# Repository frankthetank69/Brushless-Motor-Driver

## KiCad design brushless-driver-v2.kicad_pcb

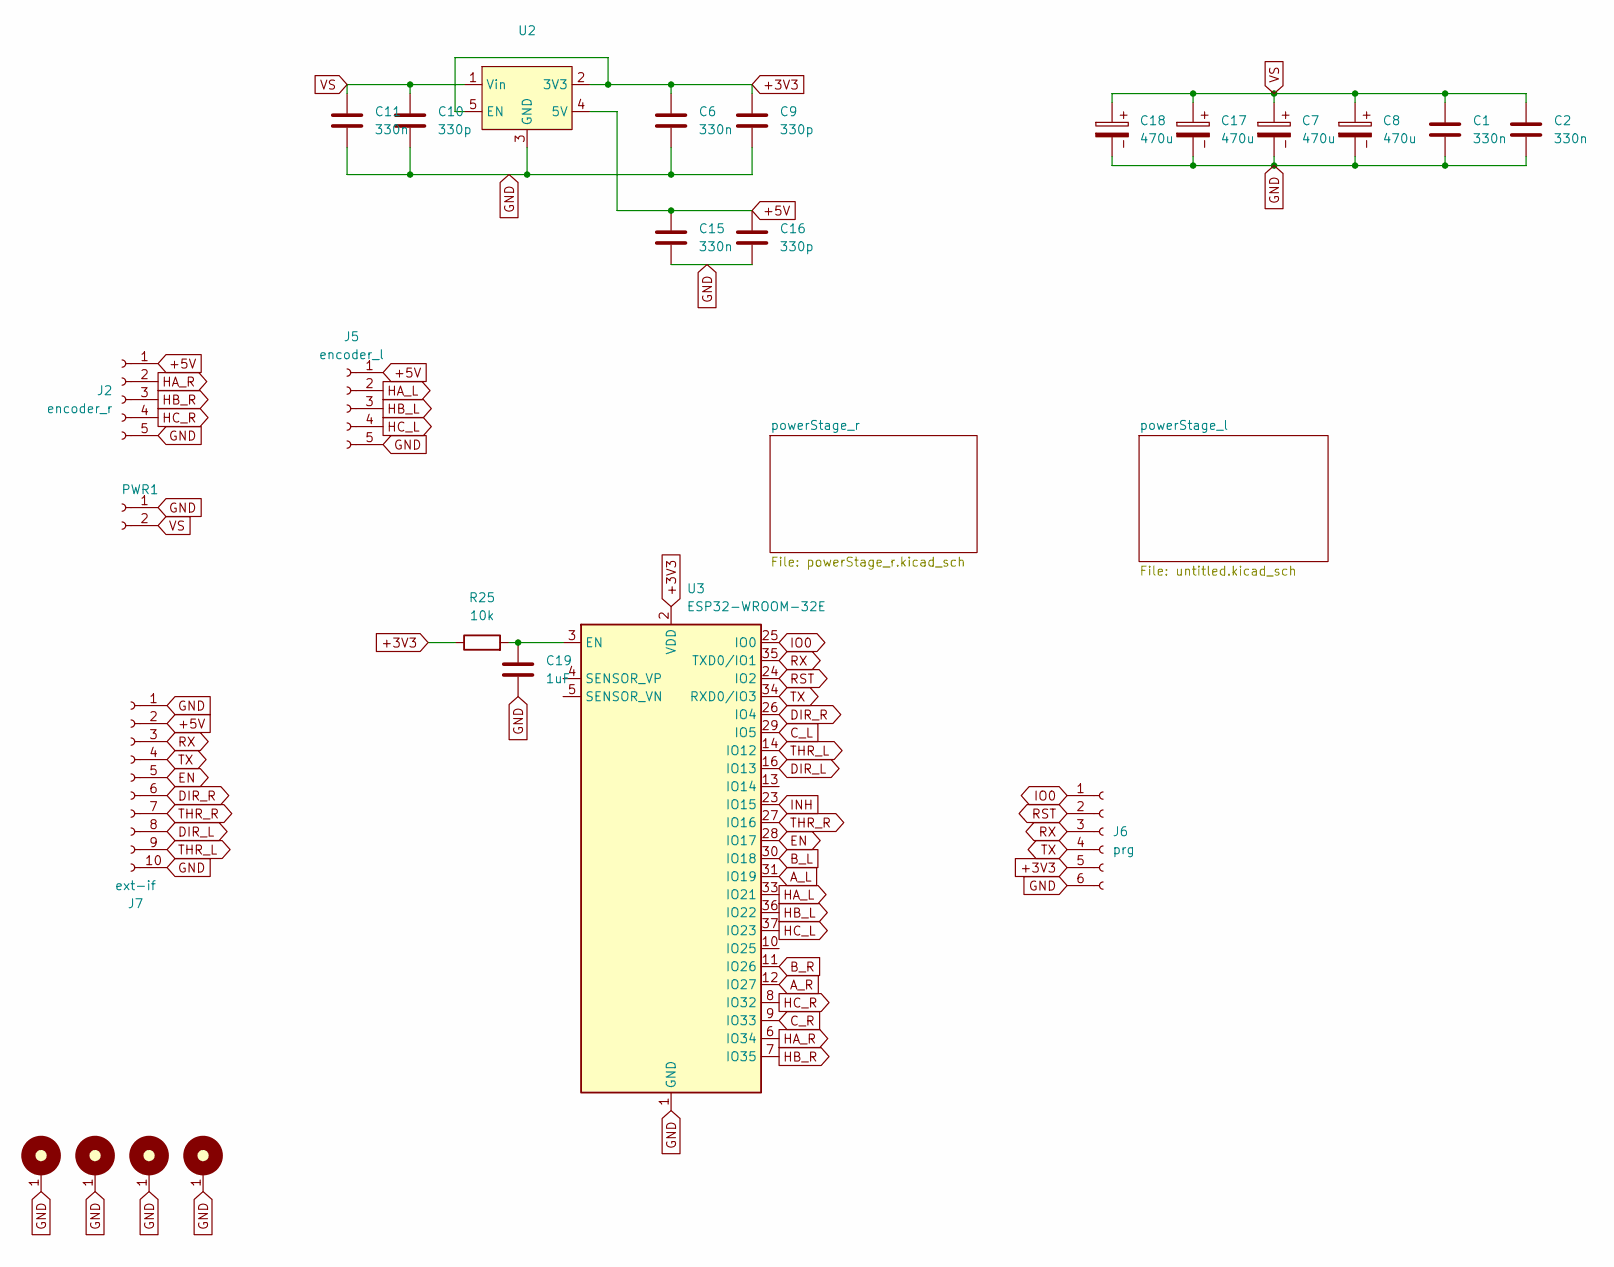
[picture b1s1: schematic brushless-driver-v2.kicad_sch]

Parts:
C1, C2, C6, C11, C15: 330n; C_0805_2012Metric_Pad1.18x1.45mm_HandSolder
C7, C8, C17, C18: 470u; CP_Radial_D10.0mm_P5.00mm
C9, C10, C16: 330p; C_0805_2012Metric_Pad1.18x1.45mm_HandSolder
C19: 1uF; C_0805_2012Metric_Pad1.18x1.45mm_HandSolder
H1, H2, H3, H4: MountingHole_M3_3.2mm_Pad; MountingHole_3.5mm_Pad_Via
J2: encoder_r; JST_PH_S5B-PH-K_1x05_P2.00mm_Horizontal
J5: encoder_l; JST_PH_S5B-PH-K_1x05_P2.00mm_Horizontal
J6: prg; Wannenstecker_6pin
J7: ext-if; Wannenstecker_10pin
PWR1: Conn_01x02_Socket; TerminalBlock_MaiXu_MX126-5.0-02P_1x02_P5.00mm
R25: 10k; R_0805_2012Metric_Pad1.20x1.40mm_HandSolder
U2: TO-252-5-11
U3: ESP32-WROOM-32E; ESP32-WROOM-32D

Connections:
+3V3: C6.1, C9.1, J6.5, R25.1, U2.2 (3V3), U2.5 (EN), U3.2 (VDD); also elsewhere on the board
+5V: C15.1, C16.1, J2.1, J5.1, J7.2, U2.4 (5V)
DIR_L: J7.8, U3.16 (IO13); also elsewhere on the board
DIR_R: J7.6, U3.26 (IO4); also elsewhere on the board
EN: J7.5, U3.28 (IO17); also elsewhere on the board
GND: C1.2, C2.2, C6.2, C7.2, C8.2, C9.2, C10.2, C11.2, C15.2, C16.2, C17.2, C18.2, C19.2, H1.1, H2.1, H3.1, H4.1, J2.5, J5.5, J6.6, J7.1, J7.10, PWR1.1, U2.3 (GND), U3.1 (GND), U3.15 (GND), U3.38 (GND), U3.39 (GND); also elsewhere on the board
HA_L: J5.2, U3.33 (IO21); also elsewhere on the board
HA_R: J2.2, U3.6 (IO34); also elsewhere on the board
HB_L: J5.3, U3.36 (IO22); also elsewhere on the board
HB_R: J2.3, U3.7 (IO35); also elsewhere on the board
HC_L: J5.4, U3.37 (IO23); also elsewhere on the board
HC_R: J2.4, U3.8 (IO32); also elsewhere on the board
IO0: J6.1, U3.25 (IO0); also elsewhere on the board
unnamed 50: C19.1, R25.2, U3.3 (EN); also elsewhere on the board
RST: J6.2, U3.24 (IO2); also elsewhere on the board
RX: J6.3, J7.3, U3.35 (TXD0/IO1); also elsewhere on the board
THR_L: J7.9, U3.14 (IO12); also elsewhere on the board
THR_R: J7.7, U3.27 (IO16); also elsewhere on the board
TX: J6.4, J7.4, U3.34 (RXD0/IO3); also elsewhere on the board
VS: C1.1, C2.1, C7.1, C8.1, C10.1, C11.1, C17.1, C18.1, PWR1.2, U2.1 (Vin); also elsewhere on the board

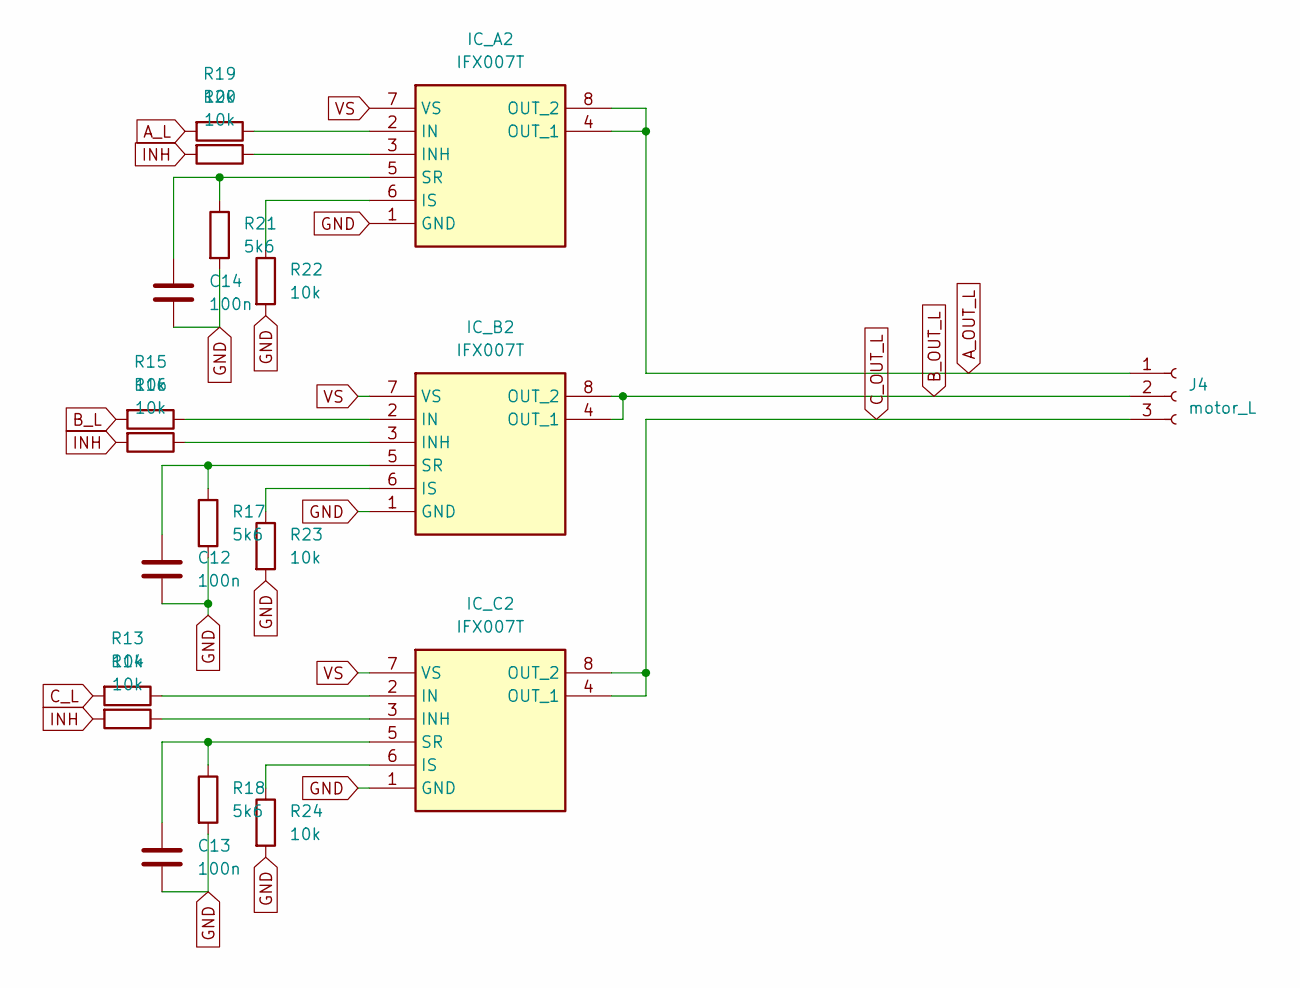
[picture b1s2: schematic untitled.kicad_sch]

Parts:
C12, C13, C14: 100n; C_0805_2012Metric_Pad1.18x1.45mm_HandSolder
IC_A2: IFX007T; TO-263-7_TabPin4; Manufacturer_Part_Number IFX007TAUMA1; Mouser Part Number 726-IFX007TAUMA1
IC_B2: IFX007T; TO-263-7_TabPin4; Manufacturer_Part_Number IFX007TAUMA1; Mouser Part Number 726-IFX007TAUMA1
IC_C2: IFX007T; TO-263-7_TabPin4; Manufacturer_Part_Number IFX007TAUMA1; Mouser Part Number 726-IFX007TAUMA1
J4: motor_L; TerminalBlock_MaiXu_MX126-5.0-03P_1x03_P5.00mm
R13, R14, R15, R16, R19, R20, R22, R23, R24: 10k; R_0805_2012Metric_Pad1.20x1.40mm_HandSolder
R17, R18, R21: 5k6; R_0805_2012Metric_Pad1.20x1.40mm_HandSolder

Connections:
A_L: R19.2; also elsewhere on the board
A_OUT_L: IC_A2.4 (OUT_1), IC_A2.8 (OUT_2), J4.1
B_L: R15.2; also elsewhere on the board
B_OUT_L: IC_B2.4 (OUT_1), IC_B2.8 (OUT_2), J4.2
C_L: R13.2; also elsewhere on the board
C_OUT_L: IC_C2.4 (OUT_1), IC_C2.8 (OUT_2), J4.3
GND: C12.2, C13.2, C14.2, IC_A2.1 (GND), IC_B2.1 (GND), IC_C2.1 (GND), R17.2, R18.2, R21.2, R22.2, R23.2, R24.2; also elsewhere on the board
INH: R14.2, R16.2, R20.2; also elsewhere on the board
unnamed: IC_A2.2 (IN), R19.1
unnamed: IC_A2.3 (INH), R20.1
unnamed: IC_A2.6 (IS), R22.1
unnamed: C14.1, IC_A2.5 (SR), R21.1
unnamed: IC_B2.2 (IN), R15.1
unnamed: IC_B2.3 (INH), R16.1
unnamed: IC_B2.6 (IS), R23.1
unnamed: C12.1, IC_B2.5 (SR), R17.1
unnamed: IC_C2.2 (IN), R13.1
unnamed: IC_C2.3 (INH), R14.1
unnamed: IC_C2.6 (IS), R24.1
unnamed: C13.1, IC_C2.5 (SR), R18.1
VS: IC_A2.7 (VS), IC_B2.7 (VS), IC_C2.7 (VS); also elsewhere on the board

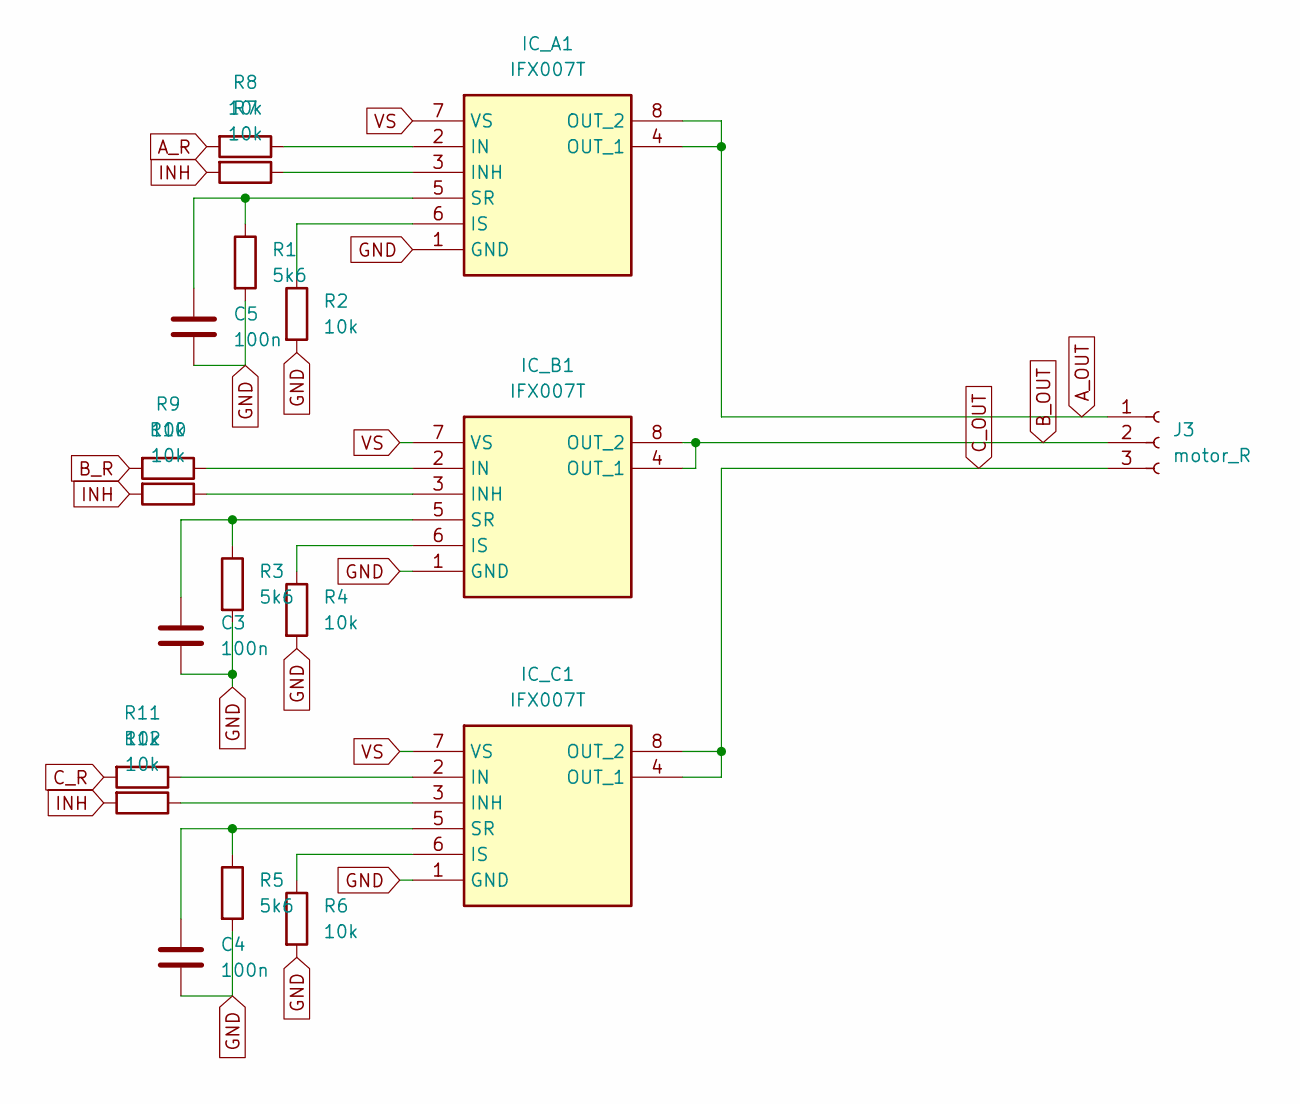
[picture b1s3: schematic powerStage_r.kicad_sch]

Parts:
C3, C4, C5: 100n; C_0805_2012Metric_Pad1.18x1.45mm_HandSolder
IC_A1: IFX007T; TO-263-7_TabPin4; Manufacturer_Part_Number IFX007TAUMA1; Mouser Part Number 726-IFX007TAUMA1
IC_B1: IFX007T; TO-263-7_TabPin4; Manufacturer_Part_Number IFX007TAUMA1; Mouser Part Number 726-IFX007TAUMA1
IC_C1: IFX007T; TO-263-7_TabPin4; Manufacturer_Part_Number IFX007TAUMA1; Mouser Part Number 726-IFX007TAUMA1
J3: motor_R; TerminalBlock_MaiXu_MX126-5.0-03P_1x03_P5.00mm
R1, R3, R5: 5k6; R_0805_2012Metric_Pad1.20x1.40mm_HandSolder
R2, R4, R6, R7, R8, R9, R10, R11, R12: 10k; R_0805_2012Metric_Pad1.20x1.40mm_HandSolder

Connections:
A_OUT: IC_A1.4 (OUT_1), IC_A1.8 (OUT_2), J3.1
A_R: R8.2; also elsewhere on the board
B_OUT: IC_B1.4 (OUT_1), IC_B1.8 (OUT_2), J3.2
B_R: R9.2; also elsewhere on the board
C_OUT: IC_C1.4 (OUT_1), IC_C1.8 (OUT_2), J3.3
C_R: R11.2; also elsewhere on the board
GND: C3.2, C4.2, C5.2, IC_A1.1 (GND), IC_B1.1 (GND), IC_C1.1 (GND), R1.2, R2.2, R3.2, R4.2, R5.2, R6.2; also elsewhere on the board
INH: R7.2, R10.2, R12.2; also elsewhere on the board
unnamed: IC_A1.2 (IN), R8.1
unnamed: IC_A1.3 (INH), R7.1
unnamed: IC_A1.6 (IS), R2.1
unnamed: C5.1, IC_A1.5 (SR), R1.1
unnamed: IC_B1.2 (IN), R9.1
unnamed: IC_B1.3 (INH), R10.1
unnamed: IC_B1.6 (IS), R4.1
unnamed: C3.1, IC_B1.5 (SR), R3.1
unnamed: IC_C1.2 (IN), R11.1
unnamed: IC_C1.3 (INH), R12.1
unnamed: IC_C1.6 (IS), R6.1
unnamed: C4.1, IC_C1.5 (SR), R5.1
VS: IC_A1.7 (VS), IC_B1.7 (VS), IC_C1.7 (VS); also elsewhere on the board

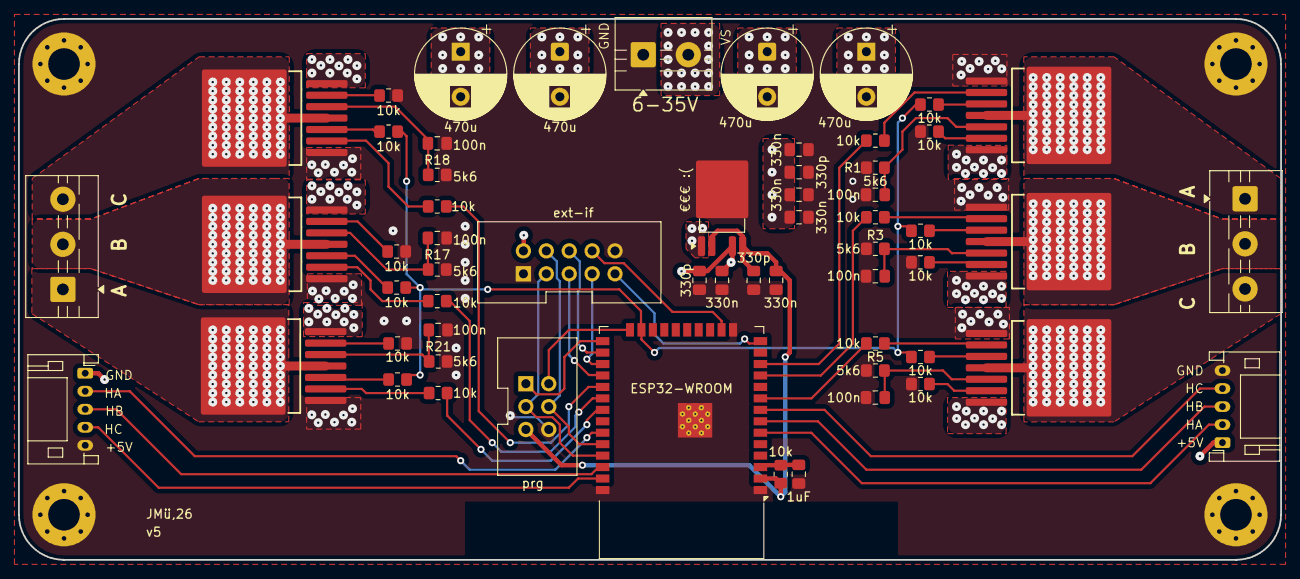
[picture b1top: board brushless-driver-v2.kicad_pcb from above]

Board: 4 copper layers, 140.0 x 60.0 mm, 63 parts (0 on the bottom side), 57 nets.

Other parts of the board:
ESP32-WROOM: ESP32-WROOM-32E; ESP32-WROOM-32D

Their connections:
+3V3: ESP32-WROOM.2 (VDD); also elsewhere on the board
A_L: ESP32-WROOM.31 (IO19); also elsewhere on the board
A_R: ESP32-WROOM.12 (IO27); also elsewhere on the board
B_L: ESP32-WROOM.30 (IO18); also elsewhere on the board
B_R: ESP32-WROOM.11 (IO26); also elsewhere on the board
C_L: ESP32-WROOM.29 (IO5); also elsewhere on the board
C_R: ESP32-WROOM.9 (IO33); also elsewhere on the board
DIR_L: ESP32-WROOM.16 (IO13); also elsewhere on the board
DIR_R: ESP32-WROOM.26 (IO4); also elsewhere on the board
EN: ESP32-WROOM.28 (IO17); also elsewhere on the board
GND: ESP32-WROOM.1 (GND), ESP32-WROOM.15 (GND), ESP32-WROOM.38 (GND), ESP32-WROOM.39 (GND); also elsewhere on the board
HA_L: ESP32-WROOM.33 (IO21); also elsewhere on the board
HA_R: ESP32-WROOM.6 (IO34); also elsewhere on the board
HB_L: ESP32-WROOM.36 (IO22); also elsewhere on the board
HB_R: ESP32-WROOM.7 (IO35); also elsewhere on the board
HC_L: ESP32-WROOM.37 (IO23); also elsewhere on the board
HC_R: ESP32-WROOM.8 (IO32); also elsewhere on the board
INH: ESP32-WROOM.23 (IO15); also elsewhere on the board
IO0: ESP32-WROOM.25 (IO0); also elsewhere on the board
unnamed 50: ESP32-WROOM.3 (EN); also elsewhere on the board
RST: ESP32-WROOM.24 (IO2); also elsewhere on the board
RX: ESP32-WROOM.35 (TXD0/IO1); also elsewhere on the board
THR_L: ESP32-WROOM.14 (IO12); also elsewhere on the board
THR_R: ESP32-WROOM.27 (IO16); also elsewhere on the board
TX: ESP32-WROOM.34 (RXD0/IO3); also elsewhere on the board
